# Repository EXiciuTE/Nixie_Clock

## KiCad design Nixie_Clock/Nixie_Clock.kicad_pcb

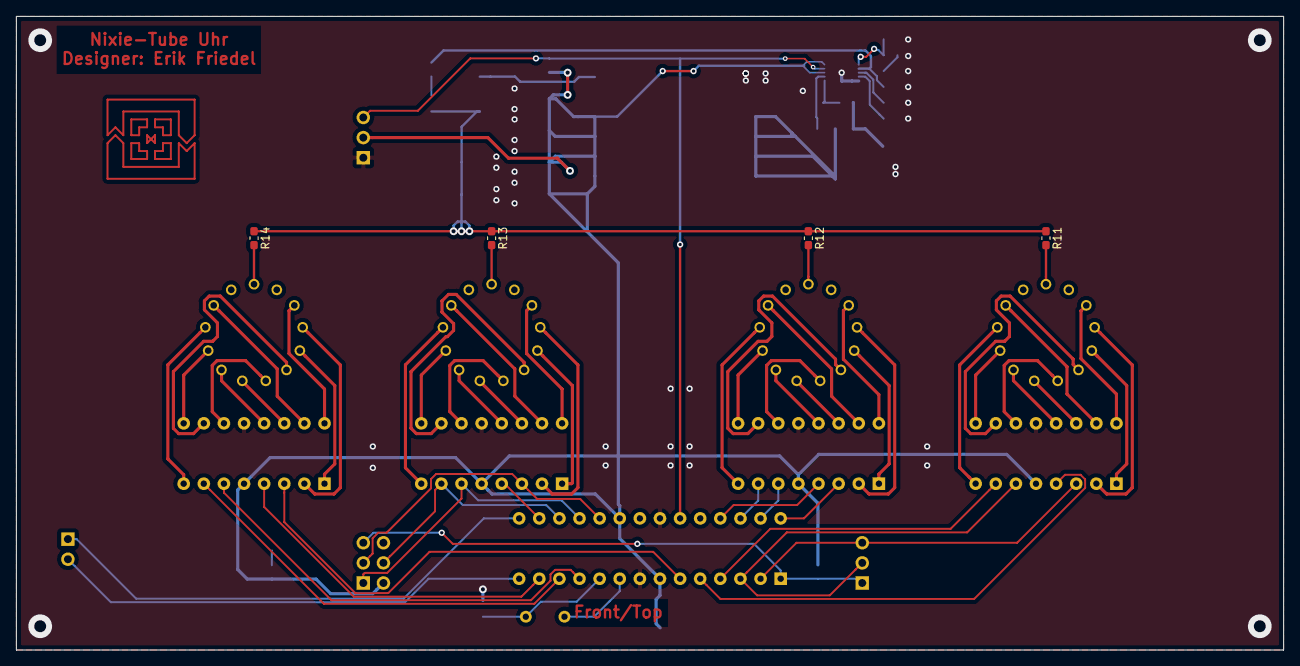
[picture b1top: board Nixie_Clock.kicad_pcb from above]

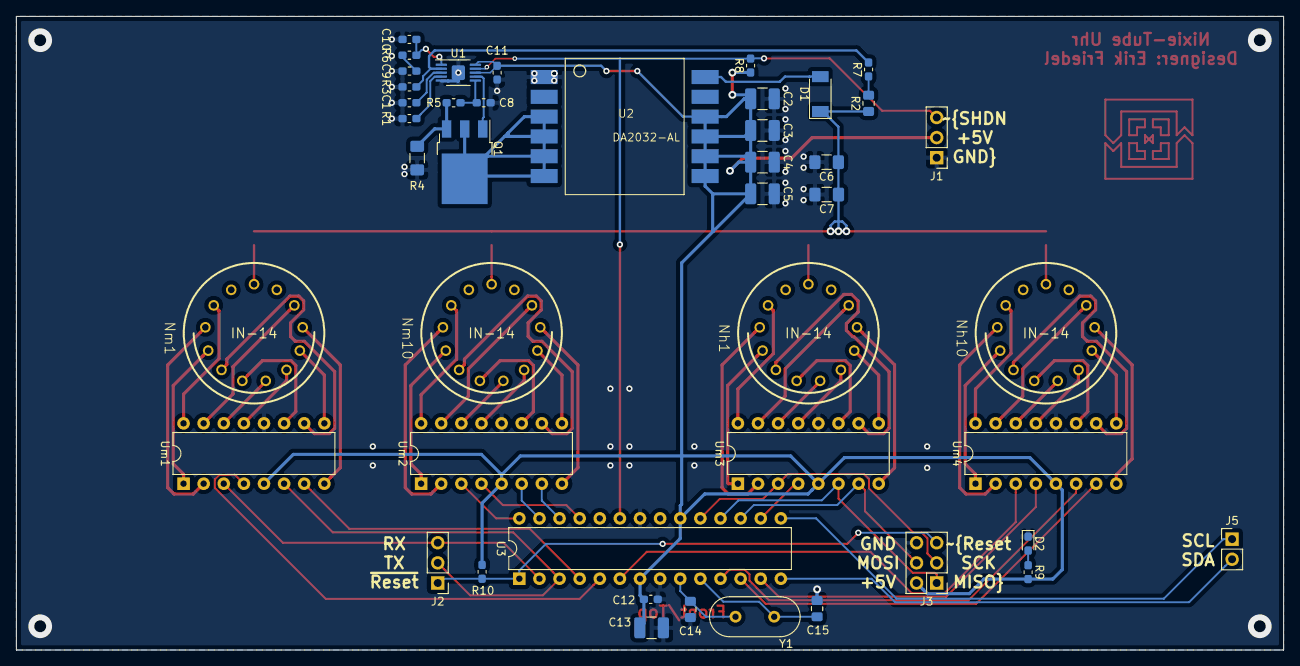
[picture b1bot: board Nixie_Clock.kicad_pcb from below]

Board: 2 copper layers, 160.0 x 80.0 mm, 48 parts (44 on the bottom side), 81 nets.

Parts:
C1: 100nF; C_0603_1608Metric_Pad1.05x0.95mm_HandSolder
C2, C3, C4, C5: 47uF 16V; C_1210_3225Metric_Pad1.42x2.65mm_HandSolder
C6, C7: 220nF 250V; C_1206_3216Metric_Pad1.42x1.75mm_HandSolder
C8: 10nF; C_0603_1608Metric_Pad1.05x0.95mm_HandSolder
C9: 22nF; C_0603_1608Metric_Pad1.05x0.95mm_HandSolder
C10: 100pF; C_0603_1608Metric_Pad1.05x0.95mm_HandSolder
C11: 10uF 16V; C_0603_1608Metric_Pad1.05x0.95mm_HandSolder
C12: 100n; C_0603_1608Metric_Pad1.05x0.95mm_HandSolder
C13: 47u; C_1210_3225Metric_Pad1.42x2.65mm_HandSolder
C14, C15: 22pF; C_0805_2012Metric_Pad1.15x1.40mm_HandSolder
D1: 600V 1A; D_SOD-128
D2: LED; D_0603_1608Metric_Pad1.05x0.95mm_HandSolder
J1: External_Power_Pins; PinHeader_1x03_P2.54mm_Vertical
J2: Serial-programmer; PinHeader_1x03_P2.54mm_Vertical
J3: AVR-ISP-6; PinHeader_2x03_P2.54mm_Vertical
J5: RTC_Pins; PinHeader_1x02_P2.54mm_Vertical
Nh1, Nh10: IN-14; nixies-us-IN-14
Nm1, Nm10: IN-14; nixies-us-IN-14
Q1: IRLR3110ZTRPBF; TO-252-3_TabPin2
R1, R8: 140k; R_0603_1608Metric_Pad1.05x0.95mm_HandSolder
R2: 1M 200V; R_0805_2012Metric_Pad1.15x1.40mm_HandSolder
R3, R6, R10, R11, R12, R13, R14: 10k; R_0603_1608Metric_Pad1.05x0.95mm_HandSolder
R4: 0,02 1W; R_1206_3216Metric_Pad1.42x1.75mm_HandSolder
R5: 22; R_0603_1608Metric_Pad1.05x0.95mm_HandSolder
R7: 63,4; R_0603_1608Metric_Pad1.05x0.95mm_HandSolder
R9: 330; R_0603_1608Metric_Pad1.05x0.95mm_HandSolder
U1: LT3757EMSE; MSOP-10-1EP_3x3mm_P0.5mm_EP1.68x1.88mm
U2: DA2032-AL
U3: ATmega328P-PU; DIP-28_W7.62mm
Um1, Um2, Um3, Um4: 74141; DIP-16_W7.62mm
Y1: Crystal; Crystal_HC49-4H_Vertical

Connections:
170V: C6.1, C7.1, D1.1, R2.1, R11.1, R12.1, R13.1, R14.1
+5V: C2.1, C3.1, C4.1, C5.1, C11.1, C12.1, C13.1, J1.2, J3.2, R8.1, R9.2, R10.1, U1.8, U1.10, U2.P$7, U2.P$8, U2.P$9, U2.P$10, U3.7, U3.20, Um1.5, Um2.5, Um3.5, Um4.5
/MISO: J3.1, U3.18, Um3.6
/MOSI: J3.4, U3.17, Um3.7
/Nixie Tube un Treiber/h04: U3.16, Um3.4
/Nixie Tube un Treiber/h11: U3.6, Um4.3
/Nixie Tube un Treiber/h12: U3.11, Um4.6
/Nixie Tube un Treiber/h13: U3.12, Um4.7
/Nixie Tube un Treiber/h14: U3.13, Um4.4
/Nixie Tube un Treiber/m03: U3.4, Um1.7
/Nixie Tube un Treiber/m04: U3.5, Um1.4
/Nixie Tube un Treiber/m11: U3.28, Um2.3
/Nixie Tube un Treiber/m12: U3.27, Um2.6
/Nixie Tube un Treiber/m13: U3.26, Um2.7
/Nixie Tube un Treiber/m14: U3.25, Um2.4
/Pin0_RX: J2.3, U3.2, Um1.3
/Pin1_TX: J2.2, U3.3, Um1.6
/SCK: J3.3, U3.19, Um3.3
/SCL: J5.1, U3.15
/SDA: J5.2, U3.14
/XTAL1: C14.2, U3.9, Y1.1
/XTAL2: C15.2, U3.10, Y1.2
GND: C1.2, C2.2, C3.2, C4.2, C5.2, C6.2, C7.2, C8.2, C9.2, C10.2, C11.2, C12.2, C13.2, C14.1, C15.1, D2.1, J1.1, J3.6, R1.2, R3.2, R4.2, U1.5, U1.11, U2.P$1, U3.8, U3.22, Um1.12, Um2.12, Um3.12, Um4.12
unnamed: C1.1, U1.3
unnamed: C8.1, R5.2, U1.6
unnamed: C9.1, R6.2
unnamed: C10.1, R6.1, U1.1
unnamed: D1.2, U2.P$12
unnamed: D2.2, R9.1
unnamed: Nh1.0, Um3.16
unnamed: Nh1.1, Um3.15
unnamed: Nh1.2, Um3.8
unnamed: Nh1.3, Um3.9
unnamed: Nh1.4, Um3.13
unnamed: Nh1.5, Um3.14
unnamed: Nh1.6, Um3.11
unnamed: Nh1.7, Um3.10
unnamed: Nh1.8, Um3.1
unnamed: Nh1.9, Um3.2
unnamed: Nh1.A, R13.2
unnamed: Nh10.0, Um4.16
unnamed: Nh10.1, Um4.15
unnamed: Nh10.2, Um4.8
unnamed: Nh10.3, Um4.9
unnamed: Nh10.4, Um4.13
unnamed: Nh10.5, Um4.14
unnamed: Nh10.6, Um4.11
unnamed: Nh10.7, Um4.10
unnamed: Nh10.8, Um4.1
unnamed: Nh10.9, Um4.2
unnamed: Nh10.A, R14.2
unnamed: Nm1.0, Um1.16
unnamed: Nm1.1, Um1.15
unnamed: Nm1.2, Um1.8
unnamed: Nm1.3, Um1.9
unnamed: Nm1.4, Um1.13
unnamed: Nm1.5, Um1.14
unnamed: Nm1.6, Um1.11
unnamed: Nm1.7, Um1.10
unnamed: Nm1.8, Um1.1
unnamed: Nm1.9, Um1.2
unnamed: Nm1.A, R11.2
unnamed: Nm10.0, Um2.16
unnamed: Nm10.1, Um2.15
unnamed: Nm10.2, Um2.8
unnamed: Nm10.3, Um2.9
unnamed: Nm10.4, Um2.13
unnamed: Nm10.5, Um2.14
unnamed: Nm10.6, Um2.11
unnamed: Nm10.7, Um2.10
unnamed: Nm10.8, Um2.1
unnamed: Nm10.9, Um2.2
unnamed: Nm10.A, R12.2
unnamed: Q1.1, U1.7
unnamed: Q1.2, U2.P$3, U2.P$4, U2.P$5, U2.P$6
unnamed: Q1.3, R4.1, R5.1
unnamed: R1.1, U1.4
unnamed: R2.2, R7.1
unnamed: R3.1, R7.2, U1.2
~Reset: J2.1, J3.5, R10.2, U3.1
~SHDN: J1.3, R8.2, U1.9, U3.23

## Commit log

2021-03-15 Add files via upload
    initial commit
